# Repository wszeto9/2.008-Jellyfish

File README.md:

# 2.008 Jellyfish
 PCA for Jellyfish themed yo-yos for my 2.008 project

# Ordering Instructions
- [Download the manufacturing data](https://github.com/wszeto9/2.008-Jellyfish/raw/main/jellyfish_lights/production.zip)
- Head to https://cart.jlcpcb.com/quote
- Click "Add Gerber File", upload the "Gerber.zip" file from the downloaded files
- Change PCB quantity to 25
- Change PCB Color to White
- Scroll down, select PCB Assembly
- By default they should be selected: Assemble top side, Economic, tooling holes added by JLCPCB, No confirm on parts placement
- Calculated price should show $30.10. Stop if this is different.
- Choose Confirm
- May ask to create an account, please do so.
- Upload BOM, CPL file. BOM file is named bom.csv, CPL file is named positions.csv
- Product description: Research\Education\DIY\Entertainment : Toy 950300
- Click next
- On top: 153 Parts detected, 153 parts confirmed. Confirm this. If numbers are off, stop and ask.
- Press next. Confirm: Price: $103.93. If this is correct, add to cart.
- Enter shipping info
- Choose DHL Express Worldwide for shipping
- Total should be $144.02 including shipping.
- For payment, you might get a $9 coupon. Feel free to use it.
- Please forward any emails within the next 24 hours if errors pop up. The parts go through human checks, and they will email you if there's issues.

# Version info:
A01: Initial design, has incorrect values for LEDs, R4, C3
A02: Updated values for LEDs, R4,C3. PCB is the same as A01, and only BOM components changed
B01: Final PCA shape (unreleased)

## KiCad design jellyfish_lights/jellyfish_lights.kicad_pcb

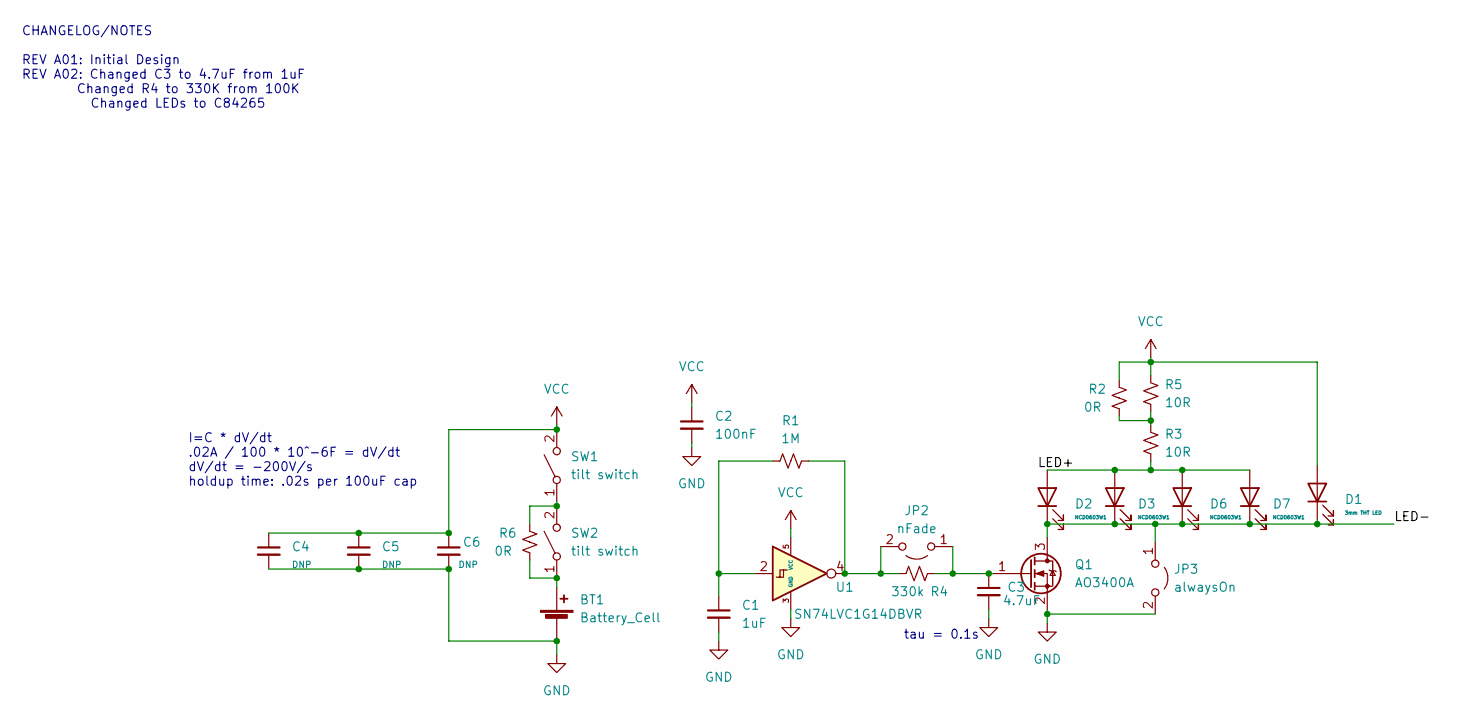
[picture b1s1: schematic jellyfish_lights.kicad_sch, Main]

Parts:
BT1: Battery_Cell; BatteryHolder_Keystone_3002_1x2032
C1: 1uF; C_0402_1005Metric; LCSC C52923
C2: 100nF; C_0402_1005Metric; LCSC C1525
C3: 4.7uF; C_0402_1005Metric; LCSC C23733
C4, C5, C6: DNP; C_1206_3216Metric
D1: 3mm THT LED; LED_D5.0mm_FlatTop; LCSC C84265
D2, D3, D6, D7: NCD0603W1; LED_0603_1608Metric; LCSC C84265
JP2: nFade; SolderJumper-2_P1.3mm_Open_TrianglePad1.0x1.5mm
JP3: alwaysOn; SolderJumper-2_P1.3mm_Open_TrianglePad1.0x1.5mm
Q1: AO3400A; SOT-23; LCSC C347475
R1: 1M; R_0402_1005Metric; LCSC C26083
R2, R6: 0R; R_0603_1608Metric; LCSC C21189
R3, R5: 10R; R_0603_1608Metric; LCSC C22859
R4: 330k; R_0402_1005Metric; LCSC C25778
SW1, SW2: tilt switch; tilt_switch
U1: SN74LVC1G14DBVR; SOT-23-5; LCSC C434069

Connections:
/LED+: D2.2 (A), D3.2 (A), D6.2 (A), D7.2 (A), R3.2
/LED-: D1.1 (K), D2.1 (K), D3.1 (K), D6.1 (K), D7.1 (K), JP3.1 (A), Q1.3 (D)
GND: BT1.2 (-), C1.2, C2.2, C3.2, C4.2, C5.2, C6.2, JP3.2 (B), Q1.2 (S), U1.3 (GND)
unnamed: BT1.1 (+), R6.1, SW2.1 (A)
unnamed: C1.1, R1.1, U1.2
unnamed: C3.1, JP2.1 (A), Q1.1 (G), R4.2
unnamed: JP2.2 (B), R1.2, R4.1, U1.4
unnamed: R2.1, R3.1, R5.2
unnamed: R6.2, SW1.1 (A), SW2.2 (B)
VCC: C2.1, C4.1, C5.1, C6.1, D1.2 (A), R2.2, R5.1, SW1.2 (B), U1.5 (VCC)

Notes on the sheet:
tau = 0.1s
I=C * dV/dt .02A / 100 * 10^-6F = dV/dt dV/dt = -200V/s holdup time: .02s per 100uF cap
CHANGELOG/NOTES REV A01: Initial Design REV A02: Changed C3 to 4.7uF from 1uF Changed R4 to 330K from 100K Changed LEDs to C84265

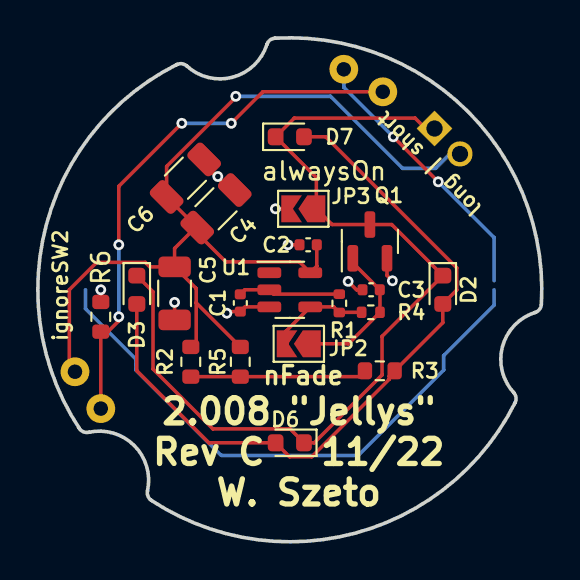
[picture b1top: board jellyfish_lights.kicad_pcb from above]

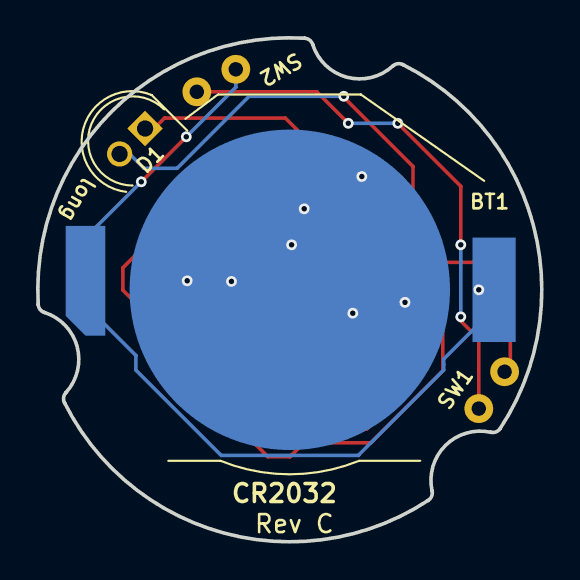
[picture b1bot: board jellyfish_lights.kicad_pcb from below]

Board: 2 copper layers, 28.0 x 28.0 mm, 24 parts (4 on the bottom side), 10 nets.

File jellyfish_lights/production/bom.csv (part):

Designator,Footprint,Quantity,Value,LCSC Part #
BT1_9,BatteryHolder_Keystone_3002_1x2032,1,Battery_Cell,
SW2_9,tilt_switch,1,tilt switch,
D1_9,LED_D5.0mm_FlatTop,1,3mm THT LED,C84265
SW2_8,tilt_switch,1,tilt switch,
SW1_9,C_Radial_D6.3mm_H5.0mm_P2.50mm,1,tilt switch,
D1_8,LED_D5.0mm_FlatTop,1,3mm THT LED,C84265
BT1_8,BatteryHolder_Keystone_3002_1x2032,1,Battery_Cell,
D1_7,LED_D5.0mm_FlatTop,1,3mm THT LED,C84265
BT1_7,BatteryHolder_Keystone_3002_1x2032,1,Battery_Cell,
SW2_7,tilt_switch,1,tilt switch,
SW1_8,C_Radial_D6.3mm_H5.0mm_P2.50mm,1,tilt switch,
SW2_6,tilt_switch,1,tilt switch,
SW1_7,C_Radial_D6.3mm_H5.0mm_P2.50mm,1,tilt switch,
BT1_6,BatteryHolder_Keystone_3002_1x2032,1,Battery_Cell,
D1_6,LED_D5.0mm_FlatTop,1,3mm THT LED,C84265
SW2_5,tilt_switch,1,tilt switch,
BT1_5,BatteryHolder_Keystone_3002_1x2032,1,Battery_Cell,
SW2_4,tilt_switch,1,tilt switch,
BT1_4,BatteryHolder_Keystone_3002_1x2032,1,Battery_Cell,
D1_5,LED_D5.0mm_FlatTop,1,3mm THT LED,C84265
BT1_3,BatteryHolder_Keystone_3002_1x2032,1,Battery_Cell,
SW2_3,tilt_switch,1,tilt switch,
D1_4,LED_D5.0mm_FlatTop,1,3mm THT LED,C84265
SW1_6,C_Radial_D6.3mm_H5.0mm_P2.50mm,1,tilt switch,
SW1_5,C_Radial_D6.3mm_H5.0mm_P2.50mm,1,tilt switch,
D1_3,LED_D5.0mm_FlatTop,1,3mm THT LED,C84265
BT1_2,BatteryHolder_Keystone_3002_1x2032,1,Battery_Cell,
D1_2,LED_D5.0mm_FlatTop,1,3mm THT LED,C84265
SW1_4,C_Radial_D6.3mm_H5.0mm_P2.50mm,1,tilt switch,
SW2_2,tilt_switch,1,tilt switch,
BT1,BatteryHolder_Keystone_3002_1x2032,1,Battery_Cell,
SW2,tilt_switch,1,tilt switch,
SW1_3,C_Radial_D6.3mm_H5.0mm_P2.50mm,1,tilt switch,
D1,LED_D5.0mm_FlatTop,1,3mm THT LED,C84265
SW1_2,C_Radial_D6.3mm_H5.0mm_P2.50mm,1,tilt switch,
SW1,C_Radial_D6.3mm_H5.0mm_P2.50mm,1,tilt switch,
D6_9,LED_0603_1608Metric,1,NCD0603W1,C84265
R2_9,R_0603_1608Metric,1,0R,C21189
JP3_9,SolderJumper-2_P1.3mm_Open_TrianglePad1.0x1.5mm,1,alwaysOn,
C4_9,C_1206_3216Metric,1,DNP,
R3_9,R_0603_1608Metric,1,10R,C22859
D2_9,LED_0603_1608Metric,1,NCD0603W1,C84265
D3_9,LED_0603_1608Metric,1,NCD0603W1,C84265
R6_9,R_0603_1608Metric,1,0R,C21189
D6_8,LED_0603_1608Metric,1,NCD0603W1,C84265
C2_9,C_0402_1005Metric,1,100nF,C1525
D3_8,LED_0603_1608Metric,1,NCD0603W1,C84265
JP3_8,SolderJumper-2_P1.3mm_Open_TrianglePad1.0x1.5mm,1,alwaysOn,
R1_9,R_0402_1005Metric,1,1M,C26083
C1_9,C_0402_1005Metric,1,1uF,C52923
D2_8,LED_0603_1608Metric,1,NCD0603W1,C84265
JP3_7,SolderJumper-2_P1.3mm_Open_TrianglePad1.0x1.5mm,1,alwaysOn,
C2_8,C_0402_1005Metric,1,100nF,C1525
JP2_9,SolderJumper-2_P1.3mm_Open_TrianglePad1.0x1.5mm,1,nFade,
C5_9,C_1206_3216Metric,1,DNP,
R2_8,R_0603_1608Metric,1,0R,C21189
C6_9,C_1206_3216Metric,1,DNP,
C5_8,C_1206_3216Metric,1,DNP,
D3_7,LED_0603_1608Metric,1,NCD0603W1,C84265
JP2_8,SolderJumper-2_P1.3mm_Open_TrianglePad1.0x1.5mm,1,nFade,
JP2_7,SolderJumper-2_P1.3mm_Open_TrianglePad1.0x1.5mm,1,nFade,
C4_8,C_1206_3216Metric,1,DNP,
C3_9,C_0402_1005Metric,1,4.7uF,C23733
R1_8,R_0402_1005Metric,1,1M,C26083
R5_9,R_0603_1608Metric,1,10R,C22859
C1_8,C_0402_1005Metric,1,1uF,C52923
C2_7,C_0402_1005Metric,1,100nF,C1525
D2_7,LED_0603_1608Metric,1,NCD0603W1,C84265
R3_8,R_0603_1608Metric,1,10R,C22859
D6_7,LED_0603_1608Metric,1,NCD0603W1,C84265
C3_8,C_0402_1005Metric,1,4.7uF,C23733
D2_6,LED_0603_1608Metric,1,NCD0603W1,C84265
C2_6,C_0402_1005Metric,1,100nF,C1525
C3_7,C_0402_1005Metric,1,4.7uF,C23733
U1_9,SOT-23-5,1,SN74LVC1G14DBVR,C434069
C1_7,C_0402_1005Metric,1,1uF,C52923
C4_7,C_1206_3216Metric,1,DNP,
Q1_9,SOT-23,1,AO3400A,C347475
R2_7,R_0603_1608Metric,1,0R,C21189
R2_6,R_0603_1608Metric,1,0R,C21189
JP3_6,SolderJumper-2_P1.3mm_Open_TrianglePad1.0x1.5mm,1,alwaysOn,
R6_8,R_0603_1608Metric,1,0R,C21189
Q1_8,SOT-23,1,AO3400A,C347475
C3_6,C_0402_1005Metric,1,4.7uF,C23733
U1_8,SOT-23-5,1,SN74LVC1G14DBVR,C434069
Q1_7,SOT-23,1,AO3400A,C347475
JP2_6,SolderJumper-2_P1.3mm_Open_TrianglePad1.0x1.5mm,1,nFade,
C4_6,C_1206_3216Metric,1,DNP,
R3_7,R_0603_1608Metric,1,10R,C22859
D2_5,LED_0603_1608Metric,1,NCD0603W1,C84265
D7_9,LED_0603_1608Metric,1,NCD0603W1,C84265
C5_7,C_1206_3216Metric,1,DNP,
R4_9,R_0402_1005Metric,1,330k,C25778
U1_7,SOT-23-5,1,SN74LVC1G14DBVR,C434069
C6_8,C_1206_3216Metric,1,DNP,
U1_6,SOT-23-5,1,SN74LVC1G14DBVR,C434069
C2_5,C_0402_1005Metric,1,100nF,C1525
R4_8,R_0402_1005Metric,1,330k,C25778
Q1_6,SOT-23,1,AO3400A,C347475
D6_6,LED_0603_1608Metric,1,NCD0603W1,C84265
D3_6,LED_0603_1608Metric,1,NCD0603W1,C84265
C1_6,C_0402_1005Metric,1,1uF,C52923
R5_8,R_0603_1608Metric,1,10R,C22859
D7_8,LED_0603_1608Metric,1,NCD0603W1,C84265
C1_5,C_0402_1005Metric,1,1uF,C52923
D6_5,LED_0603_1608Metric,1,NCD0603W1,C84265
JP3_5,SolderJumper-2_P1.3mm_Open_TrianglePad1.0x1.5mm,1,alwaysOn,
R5_7,R_0603_1608Metric,1,10R,C22859
D7_7,LED_0603_1608Metric,1,NCD0603W1,C84265
R2_5,R_0603_1608Metric,1,0R,C21189
C6_7,C_1206_3216Metric,1,DNP,
R6_7,R_0603_1608Metric,1,0R,C21189
R4_7,R_0402_1005Metric,1,330k,C25778
C4_5,C_1206_3216Metric,1,DNP,
JP2_5,SolderJumper-2_P1.3mm_Open_TrianglePad1.0x1.5mm,1,nFade,
JP3_4,SolderJumper-2_P1.3mm_Open_TrianglePad1.0x1.5mm,1,alwaysOn,
D2_4,LED_0603_1608Metric,1,NCD0603W1,C84265
C6_6,C_1206_3216Metric,1,DNP,
C1_4,C_0402_1005Metric,1,1uF,C52923
Q1_5,SOT-23,1,AO3400A,C347475
D3_5,LED_0603_1608Metric,1,NCD0603W1,C84265
U1_5,SOT-23-5,1,SN74LVC1G14DBVR,C434069
C1_3,C_0402_1005Metric,1,1uF,C52923
Q1_4,SOT-23,1,AO3400A,C347475
D7_6,LED_0603_1608Metric,1,NCD0603W1,C84265
R5_6,R_0603_1608Metric,1,10R,C22859
D6_4,LED_0603_1608Metric,1,NCD0603W1,C84265
Q1_3,SOT-23,1,AO3400A,C347475
R6_6,R_0603_1608Metric,1,0R,C21189
C4_4,C_1206_3216Metric,1,DNP,
R3_6,R_0603_1608Metric,1,10R,C22859
D3_4,LED_0603_1608Metric,1,NCD0603W1,C84265
R4_6,R_0402_1005Metric,1,330k,C25778
C6_5,C_1206_3216Metric,1,DNP,
C3_5,C_0402_1005Metric,1,4.7uF,C23733
R3_5,R_0603_1608Metric,1,10R,C22859
JP3_3,SolderJumper-2_P1.3mm_Open_TrianglePad1.0x1.5mm,1,alwaysOn,
C6_4,C_1206_3216Metric,1,DNP,
R4_5,R_0402_1005Metric,1,330k,C25778
R4_4,R_0402_1005Metric,1,330k,C25778
D6_3,LED_0603_1608Metric,1,NCD0603W1,C84265
D7_5,LED_0603_1608Metric,1,NCD0603W1,C84265
R6_5,R_0603_1608Metric,1,0R,C21189
U1_4,SOT-23-5,1,SN74LVC1G14DBVR,C434069
R3_4,R_0603_1608Metric,1,10R,C22859
C5_6,C_1206_3216Metric,1,DNP,
C5_5,C_1206_3216Metric,1,DNP,
R4_3,R_0402_1005Metric,1,330k,C25778
R6_4,R_0603_1608Metric,1,0R,C21189
Q1_2,SOT-23,1,AO3400A,C347475
C4_3,C_1206_3216Metric,1,DNP,
C5_4,C_1206_3216Metric,1,DNP,
R5_5,R_0603_1608Metric,1,10R,C22859
D3_3,LED_0603_1608Metric,1,NCD0603W1,C84265
R1_7,R_0402_1005Metric,1,1M,C26083
D6_2,LED_0603_1608Metric,1,NCD0603W1,C84265
R3_3,R_0603_1608Metric,1,10R,C22859
R1_6,R_0402_1005Metric,1,1M,C26083
C4_2,C_1206_3216Metric,1,DNP,
R4_2,R_0402_1005Metric,1,330k,C25778
C6_3,C_1206_3216Metric,1,DNP,
JP3_2,SolderJumper-2_P1.3mm_Open_TrianglePad1.0x1.5mm,1,alwaysOn,
R6_3,R_0603_1608Metric,1,0R,C21189
C1_2,C_0402_1005Metric,1,1uF,C52923
R3_2,R_0603_1608Metric,1,10R,C22859
JP3,SolderJumper-2_P1.3mm_Open_TrianglePad1.0x1.5mm,1,alwaysOn,
D7_4,LED_0603_1608Metric,1,NCD0603W1,C84265
R4,R_0402_1005Metric,1,330k,C25778
C5_3,C_1206_3216Metric,1,DNP,
C4,C_1206_3216Metric,1,DNP,
C3_4,C_0402_1005Metric,1,4.7uF,C23733
JP2_4,SolderJumper-2_P1.3mm_Open_TrianglePad1.0x1.5mm,1,nFade,
R2_4,R_0603_1608Metric,1,0R,C21189
C5_2,C_1206_3216Metric,1,DNP,
U1_3,SOT-23-5,1,SN74LVC1G14DBVR,C434069
C3_3,C_0402_1005Metric,1,4.7uF,C23733
R5_4,R_0603_1608Metric,1,10R,C22859
C3_2,C_0402_1005Metric,1,4.7uF,C23733
JP2_3,SolderJumper-2_P1.3mm_Open_TrianglePad1.0x1.5mm,1,nFade,
Q1,SOT-23,1,AO3400A,C347475
R5_3,R_0603_1608Metric,1,10R,C22859
R5_2,R_0603_1608Metric,1,10R,C22859
JP2_2,SolderJumper-2_P1.3mm_Open_TrianglePad1.0x1.5mm,1,nFade,
R2_3,R_0603_1608Metric,1,0R,C21189
C1,C_0402_1005Metric,1,1uF,C52923
C2_4,C_0402_1005Metric,1,100nF,C1525
R1_5,R_0402_1005Metric,1,1M,C26083
R2_2,R_0603_1608Metric,1,0R,C21189
R1_4,R_0402_1005Metric,1,1M,C26083
D6,LED_0603_1608Metric,1,NCD0603W1,C84265
R3,R_0603_1608Metric,1,10R,C22859
U1_2,SOT-23-5,1,SN74LVC1G14DBVR,C434069
D2_3,LED_0603_1608Metric,1,NCD0603W1,C84265
D2_2,LED_0603_1608Metric,1,NCD0603W1,C84265
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
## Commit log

2022-09-17 designed circuit
2022-09-22 created B01
    B01 has a new circuit to do blinking. The op-amp allows for fading of the lights
2022-09-22 edited BOM
    Changed C3 to 4.7uF from 1uF
    Changed R4 to 330K from 100K
    Changed LEDs to C84265
2022-10-05 Rev B01
    Changed board shape
2022-11-21 Rev C01
    -Edited THT footprints to accommodate easier soldering (moved away from BT1)
    -Added SW2 to prevent turn-on events while not spinning
2022-11-22 changed jumper to 0R resistor for ignoreSW2
2022-11-22 Updated BOM/POS file
2022-11-22 fixing LCSC numbers
